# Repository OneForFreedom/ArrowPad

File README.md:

# ArrowPad
This is arrowpad, Made for people who Use a 60% but need to use arrow keys and the 9 keys above it.

## Yummy Candy for ya eyes!

## BOM (Bill of Materials)

| BOM Name     | Quantity |
| ------------ | -------- |
| switches     | 13       |
| diode        | 13       |
| XIAO-RP2040  | 1        |
| keycap-white | 13       |

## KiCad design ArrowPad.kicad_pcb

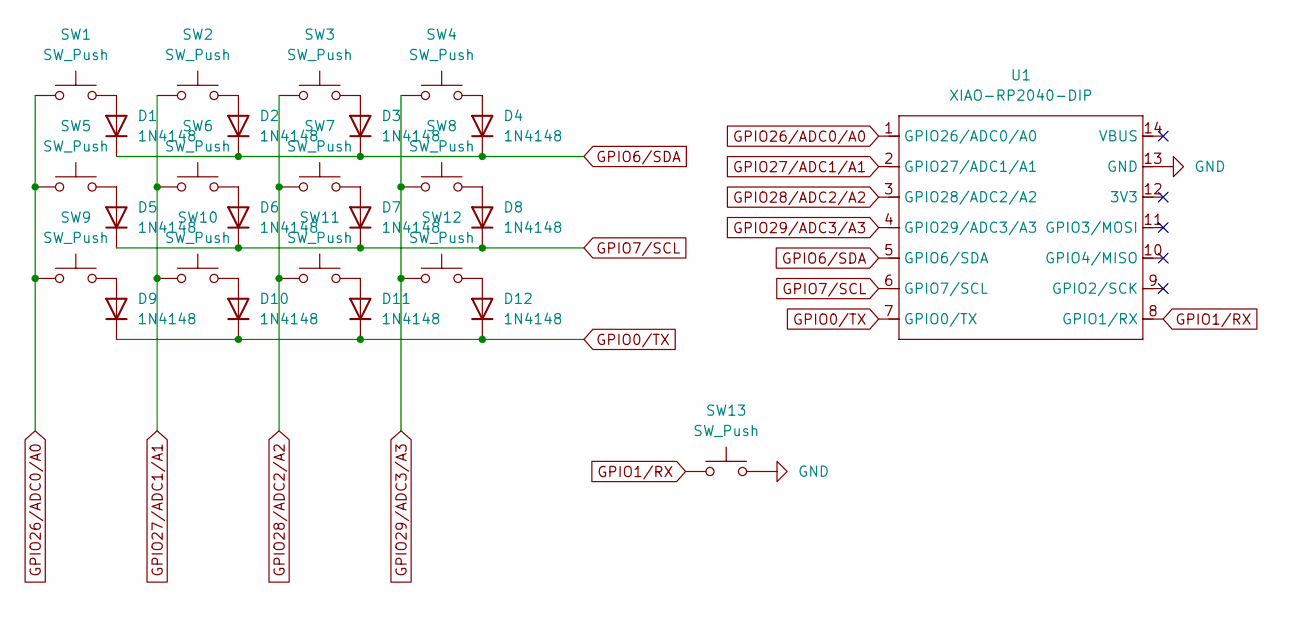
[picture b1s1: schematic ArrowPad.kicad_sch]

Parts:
D1, D2, D3, D4, D5, D6, D7, D8, D9, D10, D11, D12: 1N4148; D_DO-35_SOD27_P7.62mm_Horizontal
SW1, SW2, SW3, SW4, SW5, SW6, SW7, SW8, SW9, SW10, SW11, SW12, SW13: SW_Push; SW_Cherry_MX_1.00u_PCB WITH 3D
U1: XIAO-RP2040-DIP

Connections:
GND: SW13.2, U1.13 (GND)
GPIO0/TX: D9.1 (K), D10.1 (K), D11.1 (K), D12.1 (K), U1.7 (GPIO0/TX)
GPIO1/RX: SW13.1, U1.8 (GPIO1/RX)
GPIO6/SDA: D1.1 (K), D2.1 (K), D3.1 (K), D4.1 (K), U1.5 (GPIO6/SDA)
GPIO7/SCL: D5.1 (K), D6.1 (K), D7.1 (K), D8.1 (K), U1.6 (GPIO7/SCL)
GPIO26/ADC0/A0: SW1.1, SW5.1, SW9.1, U1.1 (GPIO26/ADC0/A0)
GPIO27/ADC1/A1: SW2.1, SW6.1, SW10.1, U1.2 (GPIO27/ADC1/A1)
GPIO28/ADC2/A2: SW3.1, SW7.1, SW11.1, U1.3 (GPIO28/ADC2/A2)
GPIO29/ADC3/A3: SW4.1, SW8.1, SW12.1, U1.4 (GPIO29/ADC3/A3)
unnamed: D1.2 (A), SW1.2
unnamed: D2.2 (A), SW2.2
unnamed: D3.2 (A), SW3.2
unnamed: D4.2 (A), SW4.2
unnamed: D5.2 (A), SW5.2
unnamed: D6.2 (A), SW6.2
unnamed: D7.2 (A), SW7.2
unnamed: D8.2 (A), SW8.2
unnamed: D9.2 (A), SW9.2
unnamed: D10.2 (A), SW10.2
unnamed: D11.2 (A), SW11.2
unnamed: D12.2 (A), SW12.2

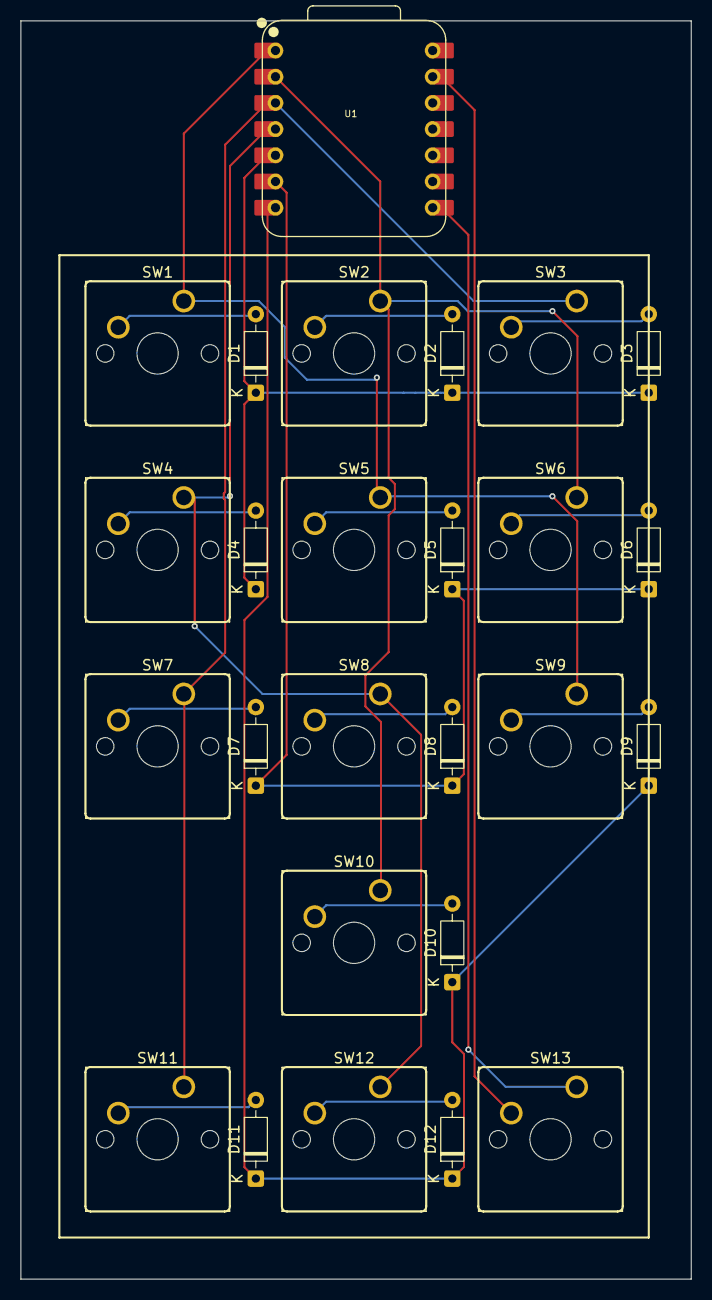
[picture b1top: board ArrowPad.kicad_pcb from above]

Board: 2 copper layers, 65.0 x 122.0 mm, 26 parts (0 on the bottom side), 21 nets.

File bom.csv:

Designator,Footprint,Quantity,Value,LCSC Part #
"D1, D10, D11, D12, D2, D3, D4, D5, D6, D7, D8, D9",D_DO-35_SOD27_P7.62mm_Horizontal,12,1N4148,
"SW1, SW10, SW11, SW12, SW13, SW2, SW3, SW4, SW5, SW6, SW7, SW8, SW9",SW_Cherry_MX_1.00u_PCB WITH 3D,13,SW_Push,
U1,XIAO-RP2040-DIP,1,XIAO-RP2040-DIP,

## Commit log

2025-08-31 Rename ArrowPad PCB.step to CAD/ArrowPad PCB.step
2025-08-31 Rename ArrowPad.zip to Production/ArrowPad.zip
2025-08-31 Rename Screenshot 2025-08-31 101202.png to Images/Screenshot 2025-08-31 101202.png
